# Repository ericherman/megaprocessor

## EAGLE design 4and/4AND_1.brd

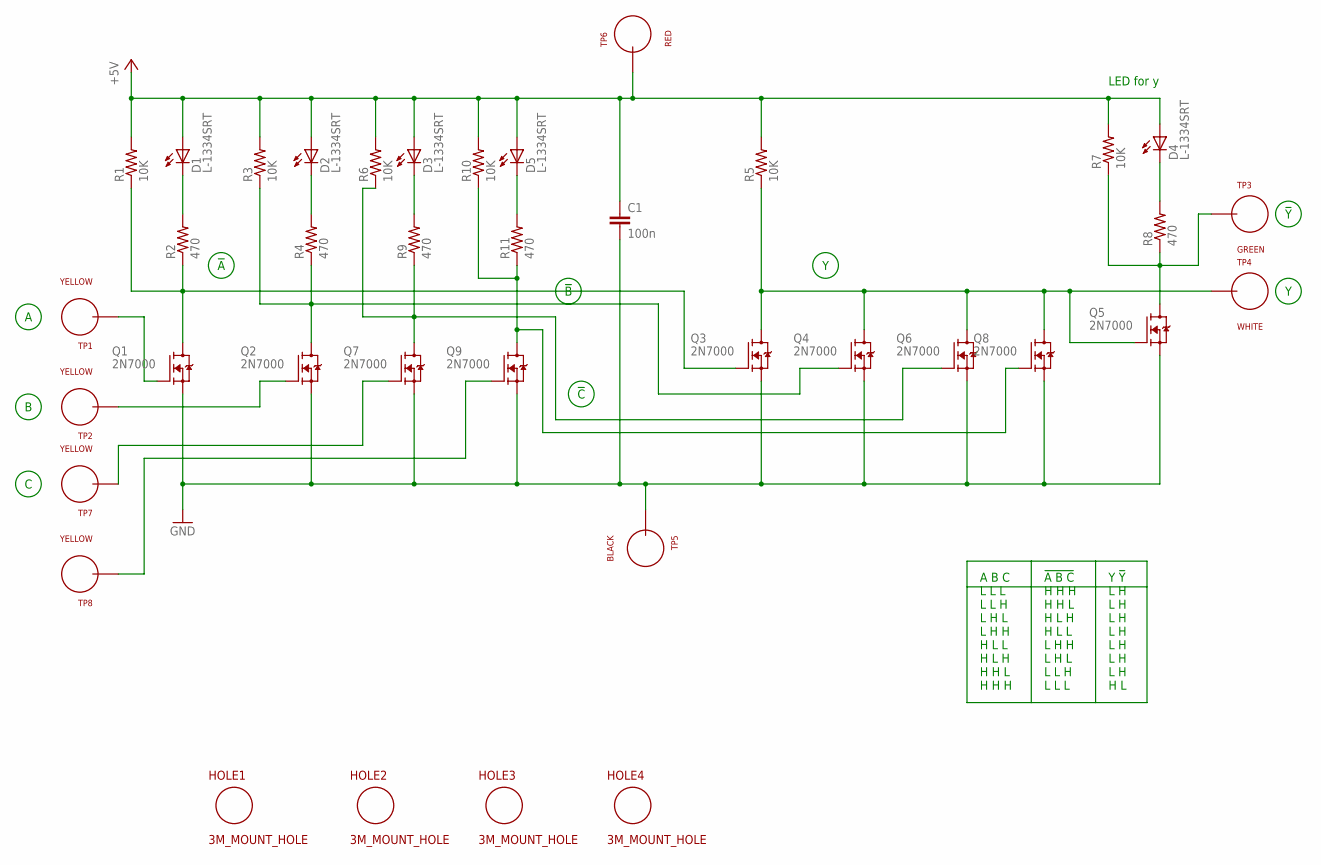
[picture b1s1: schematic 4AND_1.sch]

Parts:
C1: 100n; CAP_P2INCH
D1, D2, D3, D4, D5: L-1334SRT; LED3MM
HOLE1, HOLE2, HOLE3, HOLE4: 3M_MOUNT_HOLE; 3M_HOLE
Q1, Q2, Q3, Q4, Q5, Q6, Q7, Q8, Q9: 2N7000; TO92-DGS
R1, R3, R5, R6, R7, R10: 10K; R_P2INCH
R2, R4, R8, R9, R11: 470; R_P2INCH
TP1, TP2, TP7, TP8: YELLOW; TEST_LOOP
TP3: GREEN; TEST_LOOP
TP4: WHITE; TEST_LOOP
TP5: BLACK; TEST_LOOP
TP6: RED; TEST_LOOP

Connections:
+5V: C1.1, D1.A, D2.A, D3.A, D4.A, D5.A, R1.2, R3.2, R5.2, R6.2, R7.2, R10.2, TP6.P$1
GND: C1.2, Q1.S, Q2.S, Q3.S, Q4.S, Q5.S, Q6.S, Q7.S, Q8.S, Q9.S, TP5.P$1
unnamed: Q3.D, Q4.D, Q5.G, Q6.D, Q8.D, R5.1, TP4.P$1
unnamed: D3.K (C), R9.2
unnamed: D4.K (C), R8.2
unnamed: Q5.D, R7.1, R8.1, TP3.P$1
unnamed: Q6.G, Q7.D, R6.1, R9.1
unnamed: D2.K (C), R4.2
unnamed: Q2.D, Q4.G, R3.1, R4.1
unnamed: D1.K (C), R2.2
unnamed: Q1.D, Q3.G, R1.1, R2.1
unnamed: Q7.G, TP7.P$1
unnamed: Q1.G, TP1.P$1
unnamed: Q2.G, TP2.P$1
unnamed: D5.K (C), R11.2
unnamed: Q9.G, TP8.P$1
unnamed: Q8.G, Q9.D, R10.1, R11.1

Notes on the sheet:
A B C L L L L L H L H L L H H H L L H L H H H L H H H
!A B C H H H H H L H L H H L L L H H L H L L L H L L L
Y !Y L H L H L H L H L H L H L H H L
LED for y

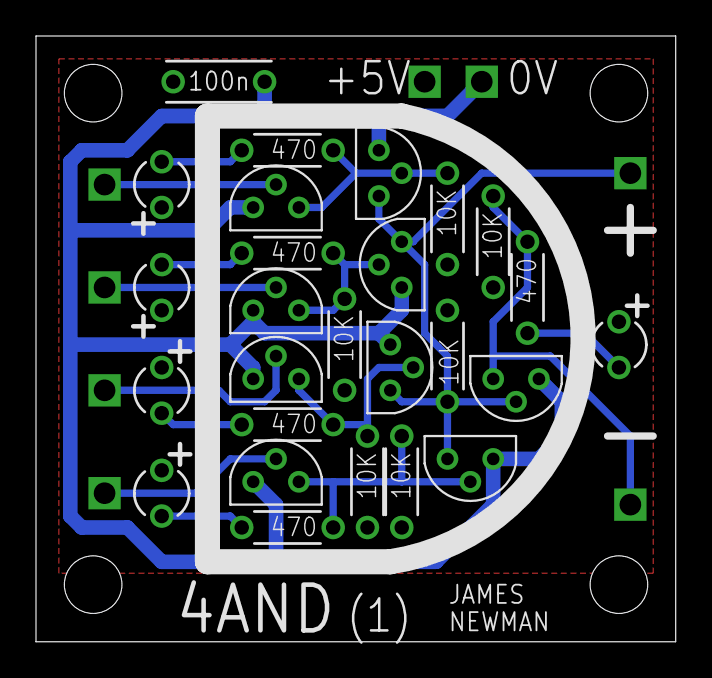
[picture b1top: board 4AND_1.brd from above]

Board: 2 copper layers, 35.5 x 33.7 mm, 38 parts (0 on the bottom side), 17 nets.

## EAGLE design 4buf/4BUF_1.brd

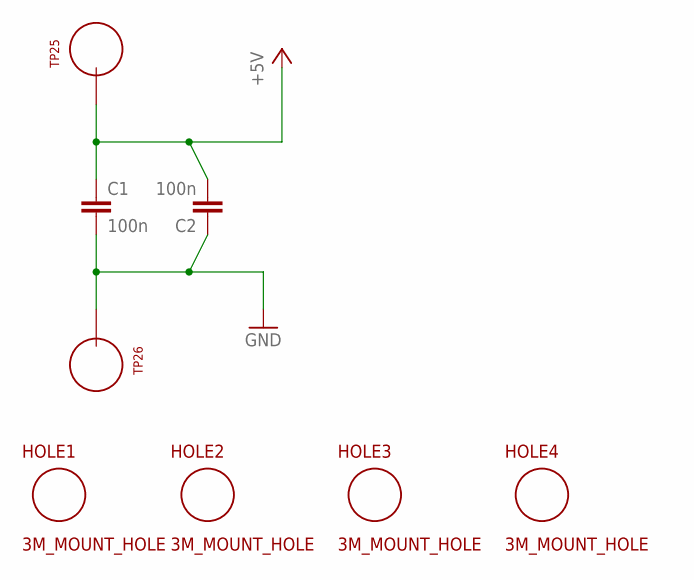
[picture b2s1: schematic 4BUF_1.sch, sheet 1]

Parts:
C1, C2: 100n; CAP_P2INCH
HOLE1, HOLE2, HOLE3, HOLE4: 3M_MOUNT_HOLE; 3M_HOLE
TP25, TP26: TEST_LOOP

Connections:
+5V: C1.1, C2.2, TP25.P$1; also elsewhere on the board
GND: C1.2, C2.1, TP26.P$1; also elsewhere on the board

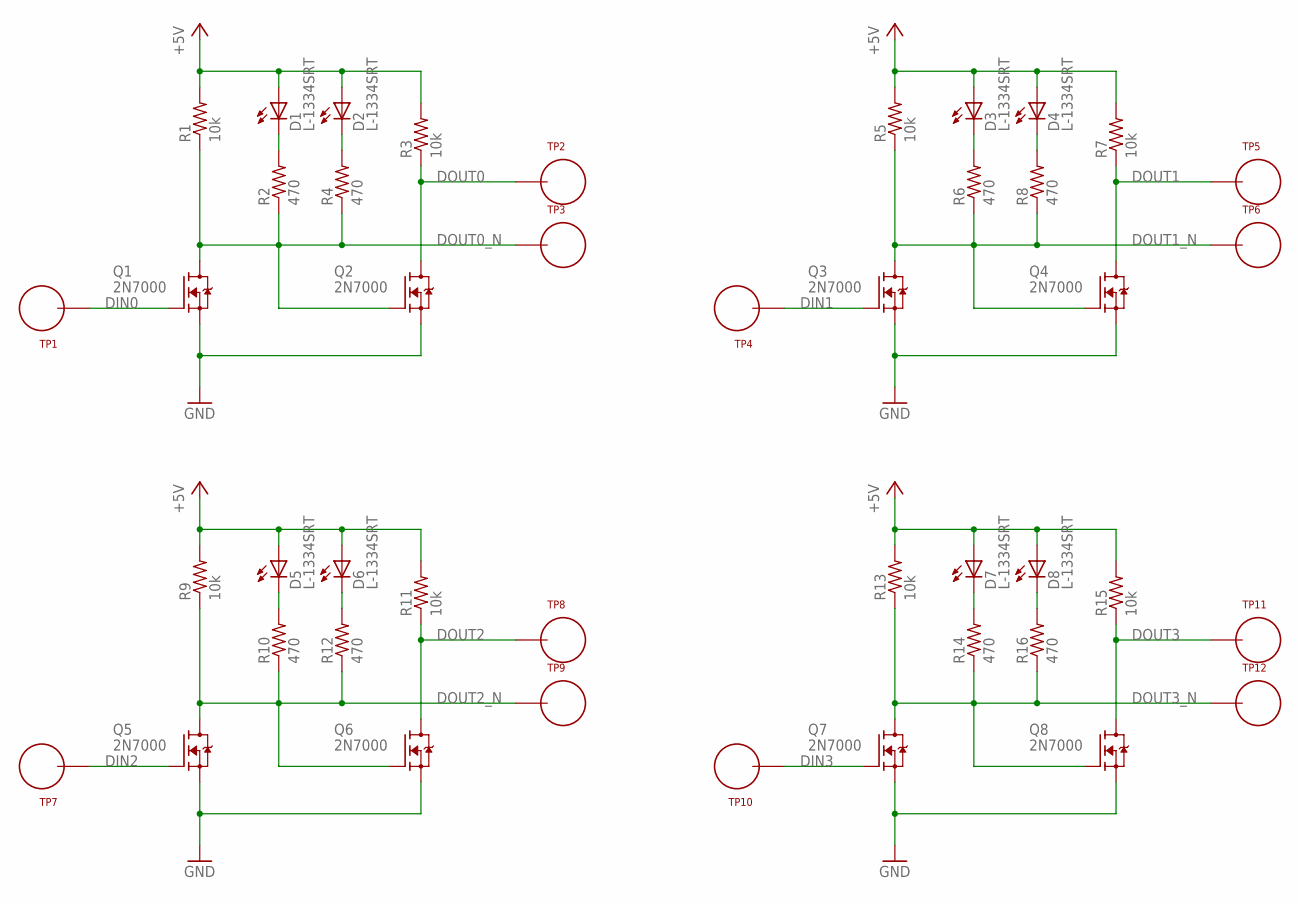
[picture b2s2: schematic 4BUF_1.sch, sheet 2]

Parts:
D1, D2, D3, D4, D5, D6, D7, D8: L-1334SRT; LED3MM
Q1, Q2, Q3, Q4, Q5, Q6, Q7, Q8: 2N7000; TO92-DGS
R1, R3, R5, R7, R9, R11, R13, R15: 10k; R_P2INCH
R2, R4, R6, R8, R10, R12, R14, R16: 470; R_P2INCH
TP1, TP2, TP3, TP4, TP5, TP6, TP7, TP8, TP9, TP10, TP11, TP12: TEST_LOOP

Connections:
+5V: D1.A, D2.A, D3.A, D4.A, D5.A, D6.A, D7.A, D8.A, R1.2, R3.2, R5.2, R7.2, R9.2, R11.2, R13.2, R15.2; also elsewhere on the board
DIN0: Q1.G, TP1.P$1
DIN1: Q3.G, TP4.P$1
DIN2: Q5.G, TP7.P$1
DIN3: Q7.G, TP10.P$1
DOUT0: Q2.D, R3.1, TP2.P$1
DOUT0_N: Q1.D, Q2.G, R1.1, R2.1, R4.1, TP3.P$1
DOUT1: Q4.D, R7.1, TP5.P$1
DOUT1_N: Q3.D, Q4.G, R5.1, R6.1, R8.1, TP6.P$1
DOUT2: Q6.D, R11.1, TP8.P$1
DOUT2_N: Q5.D, Q6.G, R9.1, R10.1, R12.1, TP9.P$1
DOUT3: Q8.D, R15.1, TP11.P$1
DOUT3_N: Q7.D, Q8.G, R13.1, R14.1, R16.1, TP12.P$1
GND: Q1.S, Q2.S, Q3.S, Q4.S, Q5.S, Q6.S, Q7.S, Q8.S; also elsewhere on the board
unnamed: D2.K (C), R4.2
unnamed: D1.K (C), R2.2
unnamed: D3.K (C), R6.2
unnamed: D4.K (C), R8.2
unnamed: D5.K (C), R10.2
unnamed: D6.K (C), R12.2
unnamed: D7.K (C), R14.2
unnamed: D8.K (C), R16.2

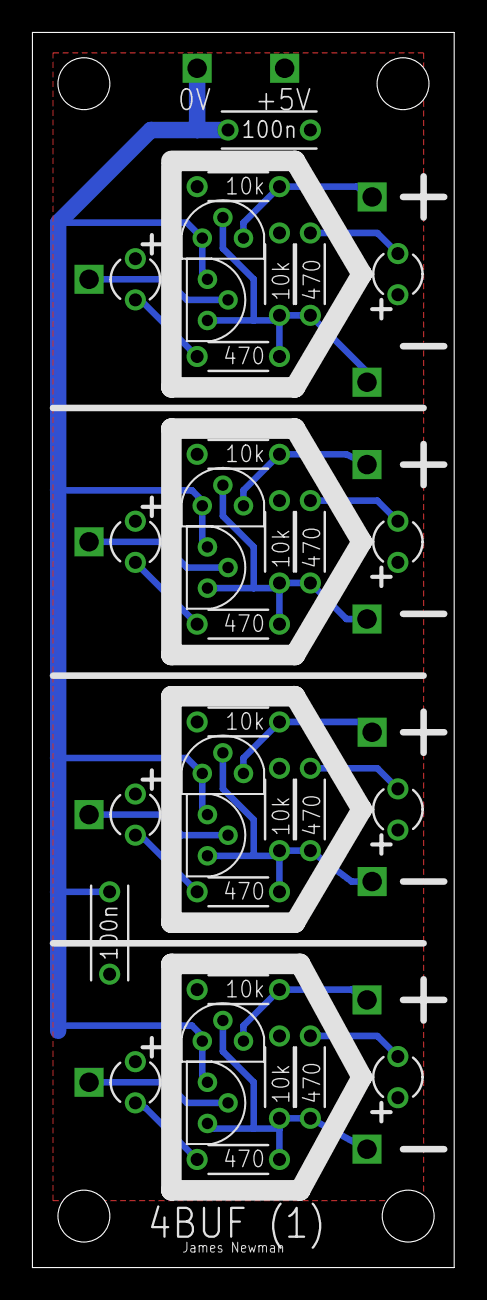
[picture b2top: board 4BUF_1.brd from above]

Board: 2 copper layers, 26.0 x 76.2 mm, 52 parts (0 on the bottom side), 22 nets.

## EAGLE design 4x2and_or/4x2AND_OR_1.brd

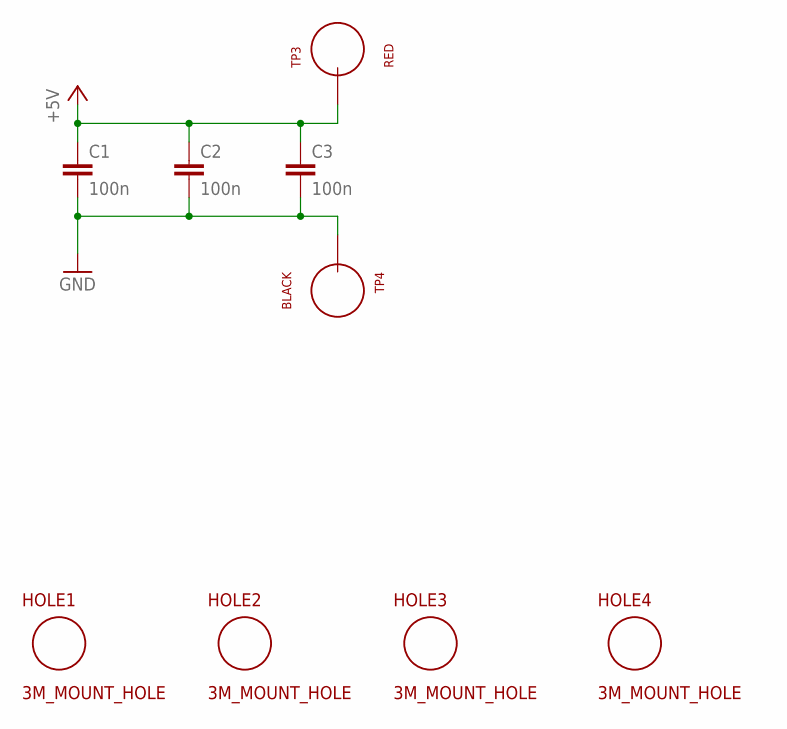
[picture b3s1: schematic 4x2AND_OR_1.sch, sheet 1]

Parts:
C1, C2, C3: 100n; CAP_P2INCH
HOLE1, HOLE2, HOLE3, HOLE4: 3M_MOUNT_HOLE; 3M_HOLE
TP3: RED; TEST_LOOP
TP4: BLACK; TEST_LOOP

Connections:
+5V: C1.1, C2.1, C3.1, TP3.P$1; also elsewhere on the board
GND: C1.2, C2.2, C3.2, TP4.P$1; also elsewhere on the board

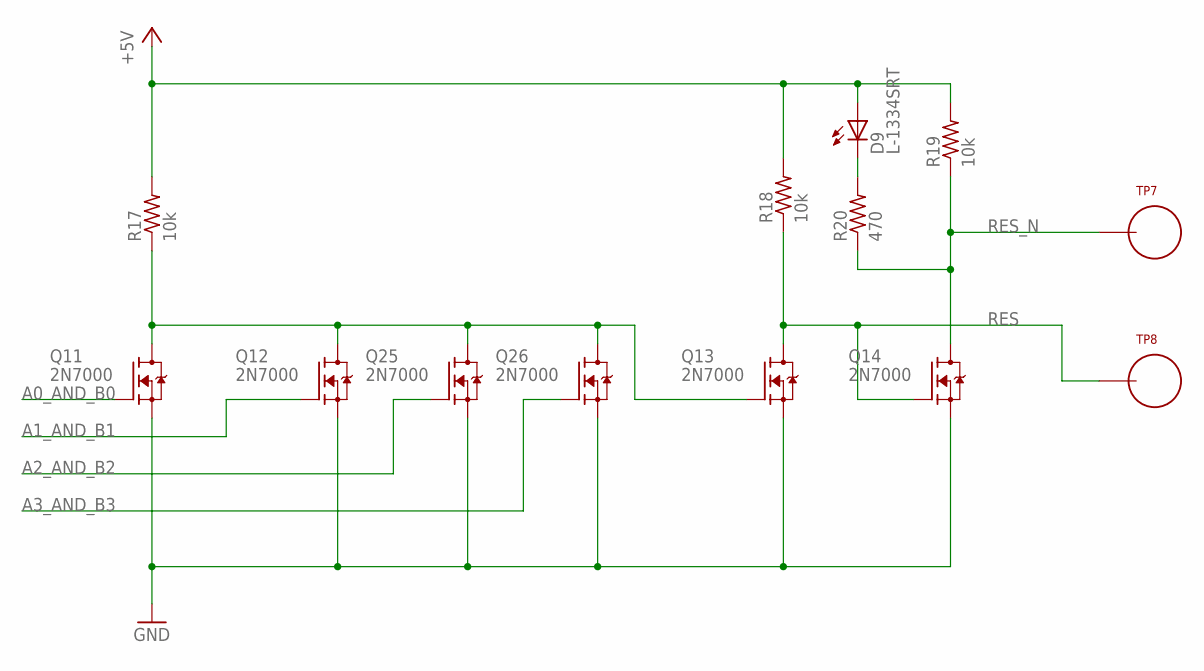
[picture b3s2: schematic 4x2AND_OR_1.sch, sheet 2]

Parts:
D9: L-1334SRT; LED3MM
Q11, Q12, Q13, Q14, Q25, Q26: 2N7000; TO92-DGS
R17, R18, R19: 10k; R_P2INCH
R20: 470; R_P2INCH
TP7, TP8: TEST_LOOP

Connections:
+5V: D9.A, R17.2, R18.2, R19.2; also elsewhere on the board
A0_AND_B0: Q11.G; also elsewhere on the board
A1_AND_B1: Q12.G; also elsewhere on the board
A2_AND_B2: Q25.G; also elsewhere on the board
A3_AND_B3: Q26.G; also elsewhere on the board
GND: Q11.S, Q12.S, Q13.S, Q14.S, Q25.S, Q26.S; also elsewhere on the board
unnamed: Q11.D, Q12.D, Q13.G, Q25.D, Q26.D, R17.1
unnamed: D9.K (C), R20.2
RES: Q13.D, Q14.G, R18.1, TP8.P$1
RES_N: Q14.D, R19.1, R20.1, TP7.P$1

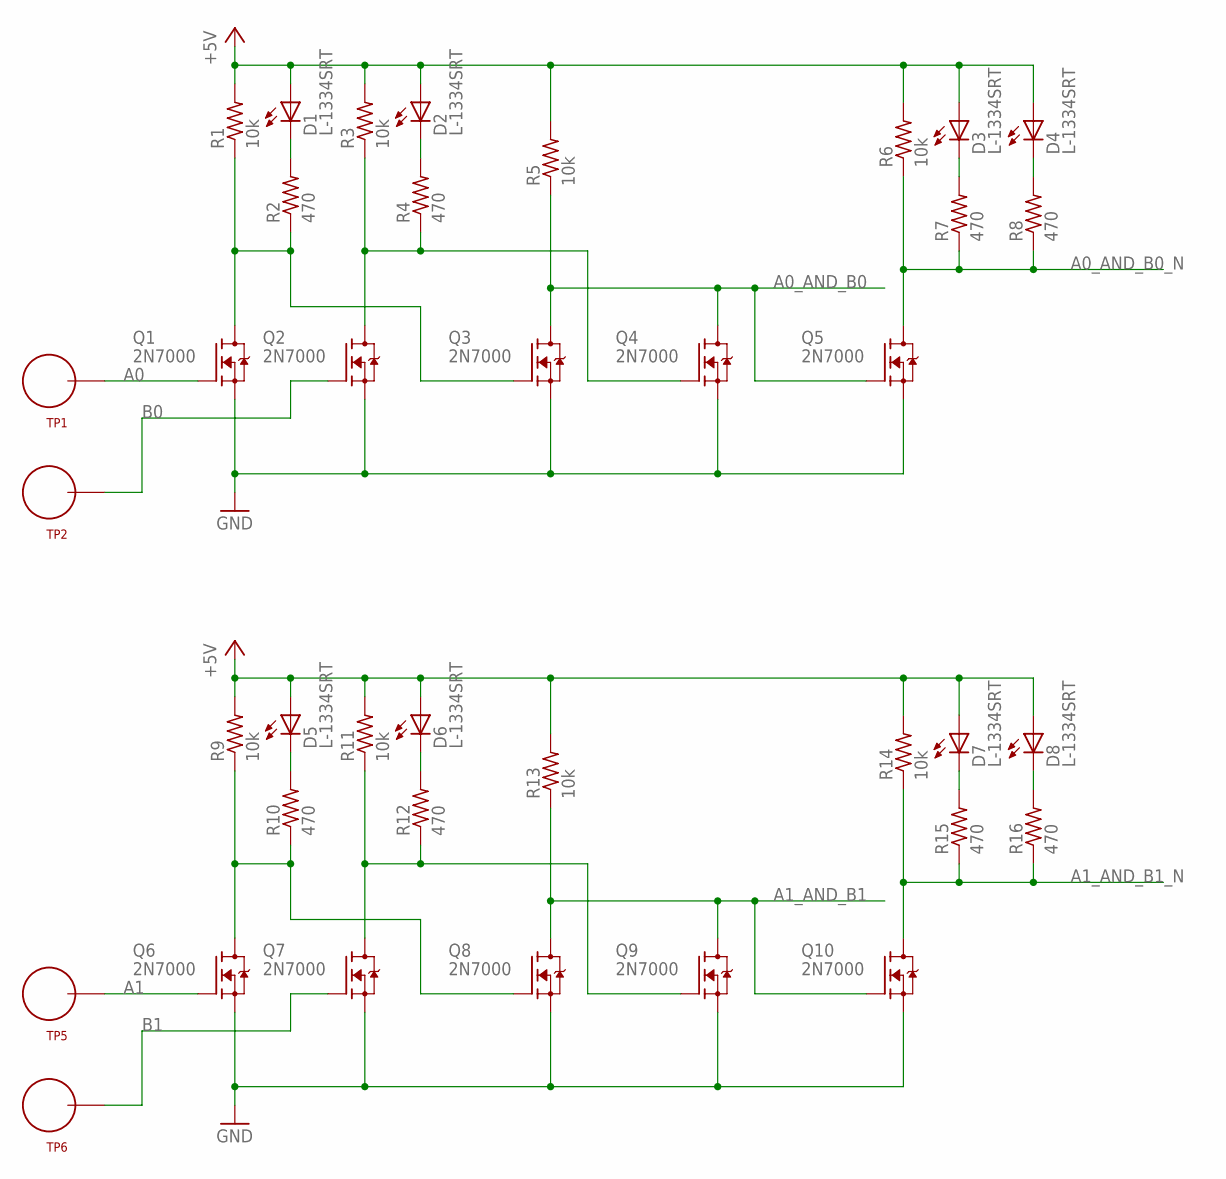
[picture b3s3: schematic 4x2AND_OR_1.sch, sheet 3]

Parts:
D1, D2, D3, D4, D5, D6, D7, D8: L-1334SRT; LED3MM
Q1, Q2, Q3, Q4, Q5, Q6, Q7, Q8, Q9, Q10: 2N7000; TO92-DGS
R1, R3, R5, R6, R9, R11, R13, R14: 10k; R_P2INCH
R2, R4, R7, R8, R10, R12, R15, R16: 470; R_P2INCH
TP1, TP2, TP5, TP6: TEST_LOOP

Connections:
+5V: D1.A, D2.A, D3.A, D4.A, D5.A, D6.A, D7.A, D8.A, R1.2, R3.2, R5.2, R6.2, R9.2, R11.2, R13.2, R14.2; also elsewhere on the board
A0: Q1.G, TP1.P$1
A0_AND_B0: Q3.D, Q4.D, Q5.G, R5.1; also elsewhere on the board
A0_AND_B0_N: Q5.D, R6.1, R7.1, R8.1
A1: Q6.G, TP5.P$1
A1_AND_B1: Q8.D, Q9.D, Q10.G, R13.1; also elsewhere on the board
A1_AND_B1_N: Q10.D, R14.1, R15.1, R16.1
B0: Q2.G, TP2.P$1
B1: Q7.G, TP6.P$1
GND: Q1.S, Q2.S, Q3.S, Q4.S, Q5.S, Q6.S, Q7.S, Q8.S, Q9.S, Q10.S; also elsewhere on the board
unnamed: D1.K (C), R2.2
unnamed: Q1.D, Q3.G, R1.1, R2.1
unnamed: D4.K (C), R8.2
unnamed: D2.K (C), R4.2
unnamed: Q2.D, Q4.G, R3.1, R4.1
unnamed: D5.K (C), R10.2
unnamed: Q6.D, Q8.G, R9.1, R10.1
unnamed: D6.K (C), R12.2
unnamed: D3.K (C), R7.2
unnamed: Q7.D, Q9.G, R11.1, R12.1
unnamed: D7.K (C), R15.2
unnamed: D8.K (C), R16.2

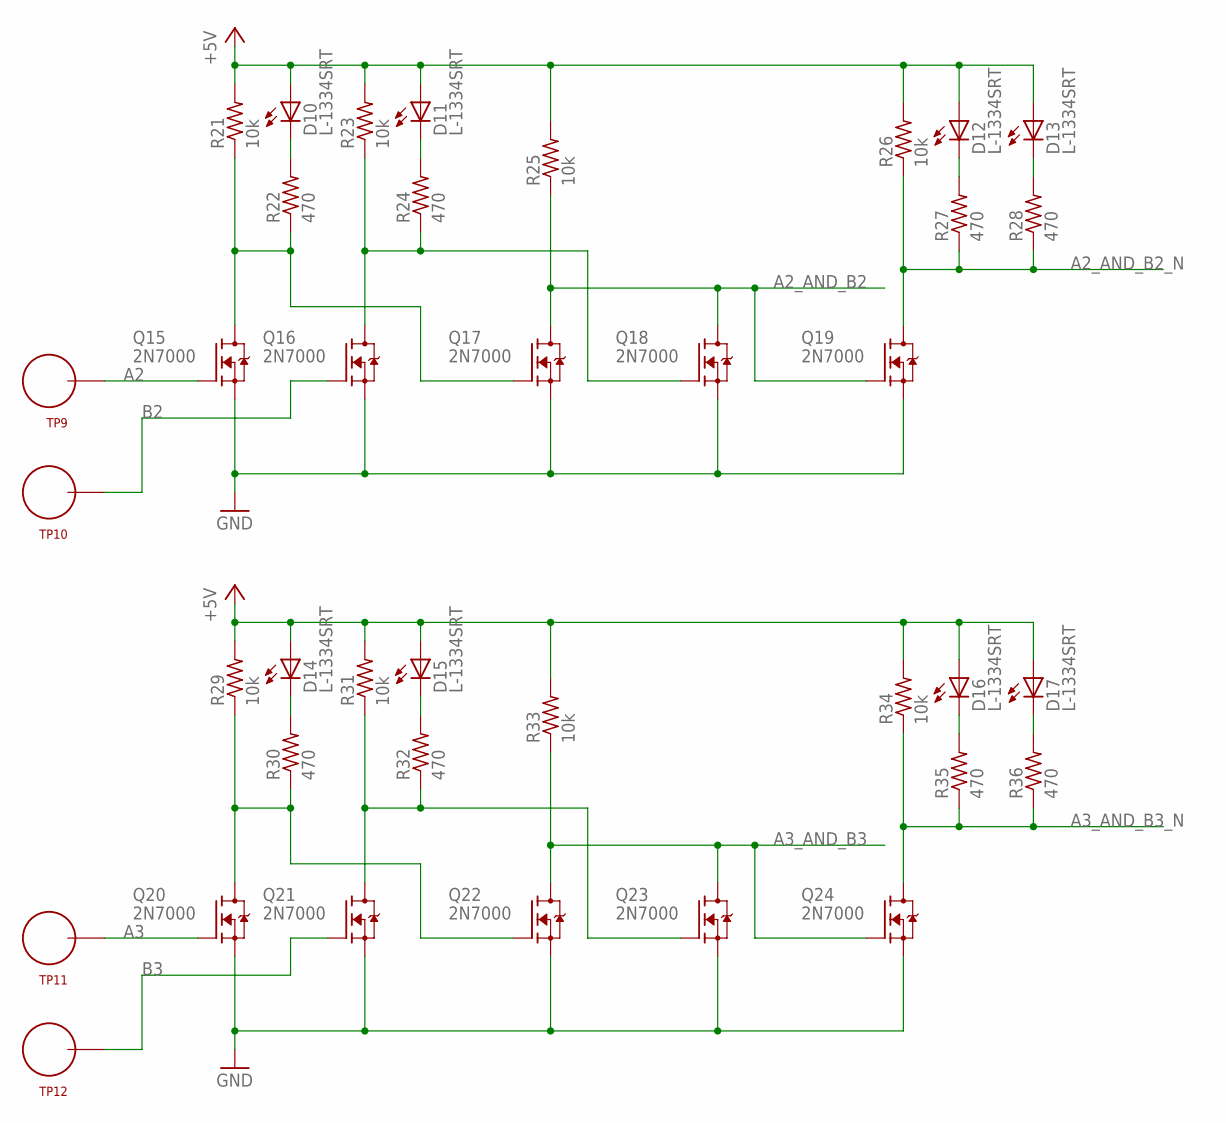
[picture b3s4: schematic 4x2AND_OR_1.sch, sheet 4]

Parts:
D10, D11, D12, D13, D14, D15, D16, D17: L-1334SRT; LED3MM
Q15, Q16, Q17, Q18, Q19, Q20, Q21, Q22, Q23, Q24: 2N7000; TO92-DGS
R21, R23, R25, R26, R29, R31, R33, R34: 10k; R_P2INCH
R22, R24, R27, R28, R30, R32, R35, R36: 470; R_P2INCH
TP9, TP10, TP11, TP12: TEST_LOOP

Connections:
+5V: D10.A, D11.A, D12.A, D13.A, D14.A, D15.A, D16.A, D17.A, R21.2, R23.2, R25.2, R26.2, R29.2, R31.2, R33.2, R34.2; also elsewhere on the board
A2: Q15.G, TP9.P$1
A2_AND_B2: Q17.D, Q18.D, Q19.G, R25.1; also elsewhere on the board
A2_AND_B2_N: Q19.D, R26.1, R27.1, R28.1
A3: Q20.G, TP11.P$1
A3_AND_B3: Q22.D, Q23.D, Q24.G, R33.1; also elsewhere on the board
A3_AND_B3_N: Q24.D, R34.1, R35.1, R36.1
B2: Q16.G, TP10.P$1
B3: Q21.G, TP12.P$1
GND: Q15.S, Q16.S, Q17.S, Q18.S, Q19.S, Q20.S, Q21.S, Q22.S, Q23.S, Q24.S; also elsewhere on the board
unnamed: D10.K (C), R22.2
unnamed: Q15.D, Q17.G, R21.1, R22.1
unnamed: D11.K (C), R24.2
unnamed: Q16.D, Q18.G, R23.1, R24.1
unnamed: D12.K (C), R27.2
unnamed: D13.K (C), R28.2
unnamed: D14.K (C), R30.2
unnamed: Q20.D, Q22.G, R29.1, R30.1
unnamed: D15.K (C), R32.2
unnamed: Q21.D, Q23.G, R31.1, R32.1
unnamed: D16.K (C), R35.2
unnamed: D17.K (C), R36.2

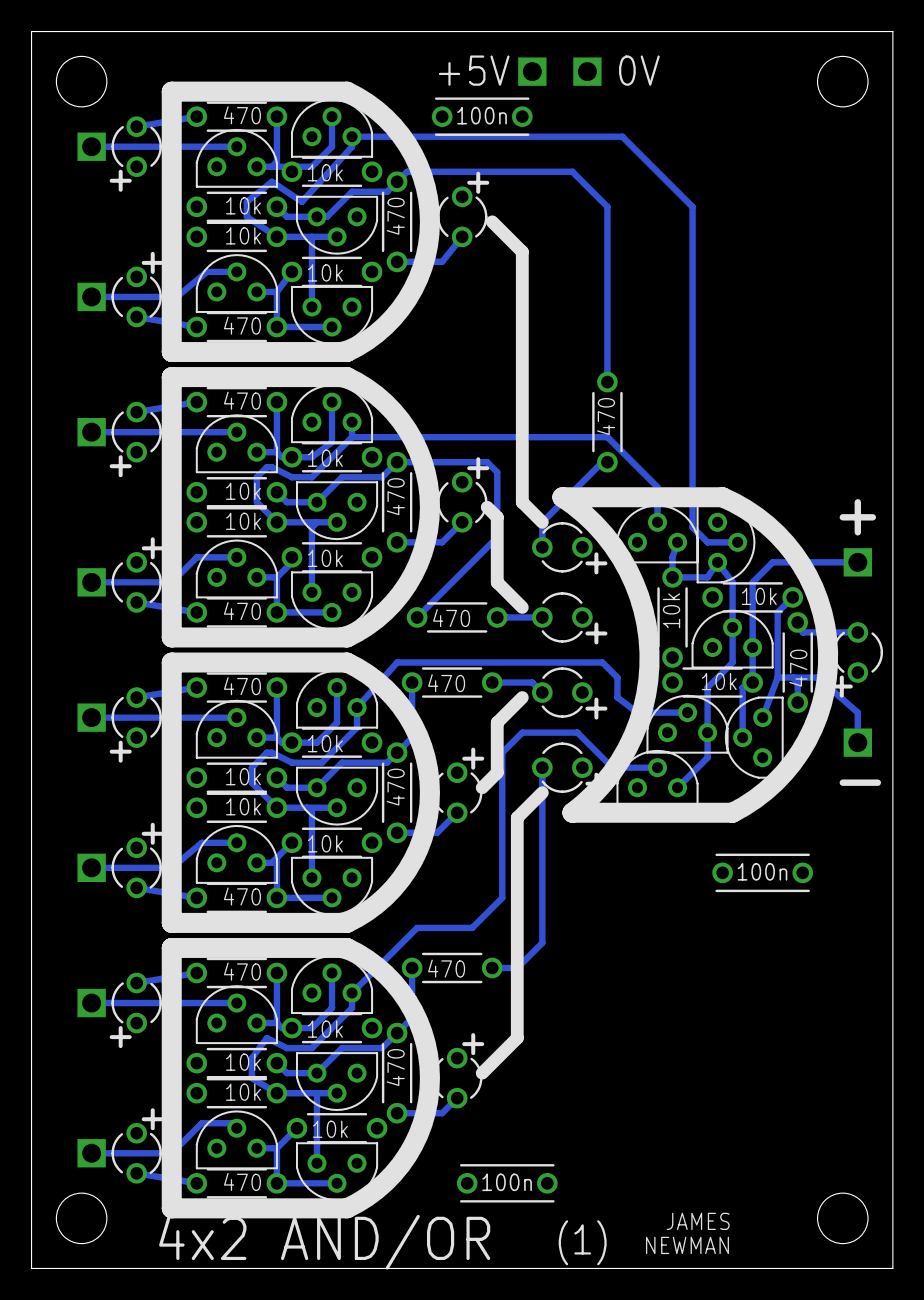
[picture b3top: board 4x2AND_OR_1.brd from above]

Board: 4 copper layers, 54.6 x 78.4 mm, 98 parts (0 on the bottom side), 46 nets.

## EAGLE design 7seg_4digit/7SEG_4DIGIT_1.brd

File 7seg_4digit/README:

3x2, 4DIGITS

Same board, there's two ways of fitting the display.

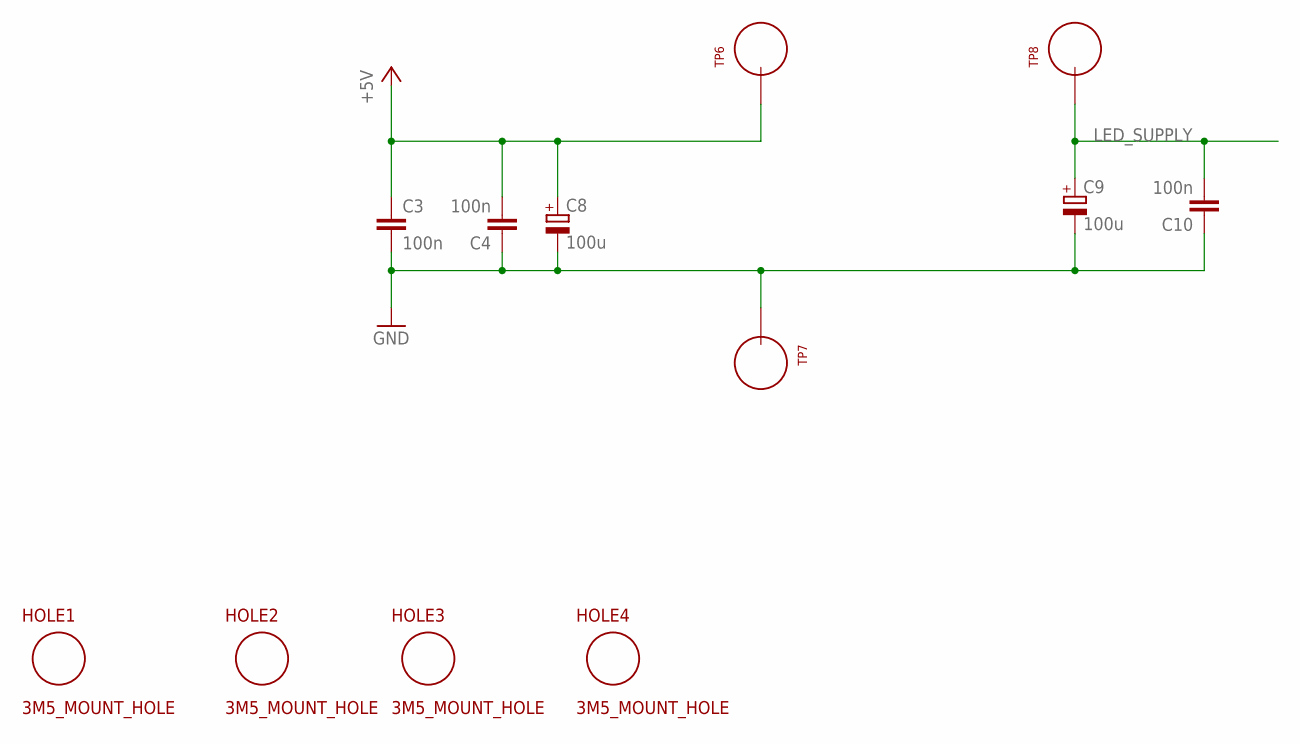
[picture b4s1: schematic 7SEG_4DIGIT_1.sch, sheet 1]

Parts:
C3, C4, C10: 100n; CAP_P2INCH
C8, C9: 100u; POLARISED_CAP_2P5_6P3MM
HOLE1, HOLE2, HOLE3, HOLE4: 3M5_MOUNT_HOLE; 3P5M_HOLE
TP6, TP7, TP8: TEST_LOOP

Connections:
+5V: C3.1, C4.2, C8.A, TP6.P$1; also elsewhere on the board
GND: C3.2, C4.1, C8.K, C9.K, C10.1, TP7.P$1; also elsewhere on the board
LED_SUPPLY: C9.A, C10.2, TP8.P$1; also elsewhere on the board

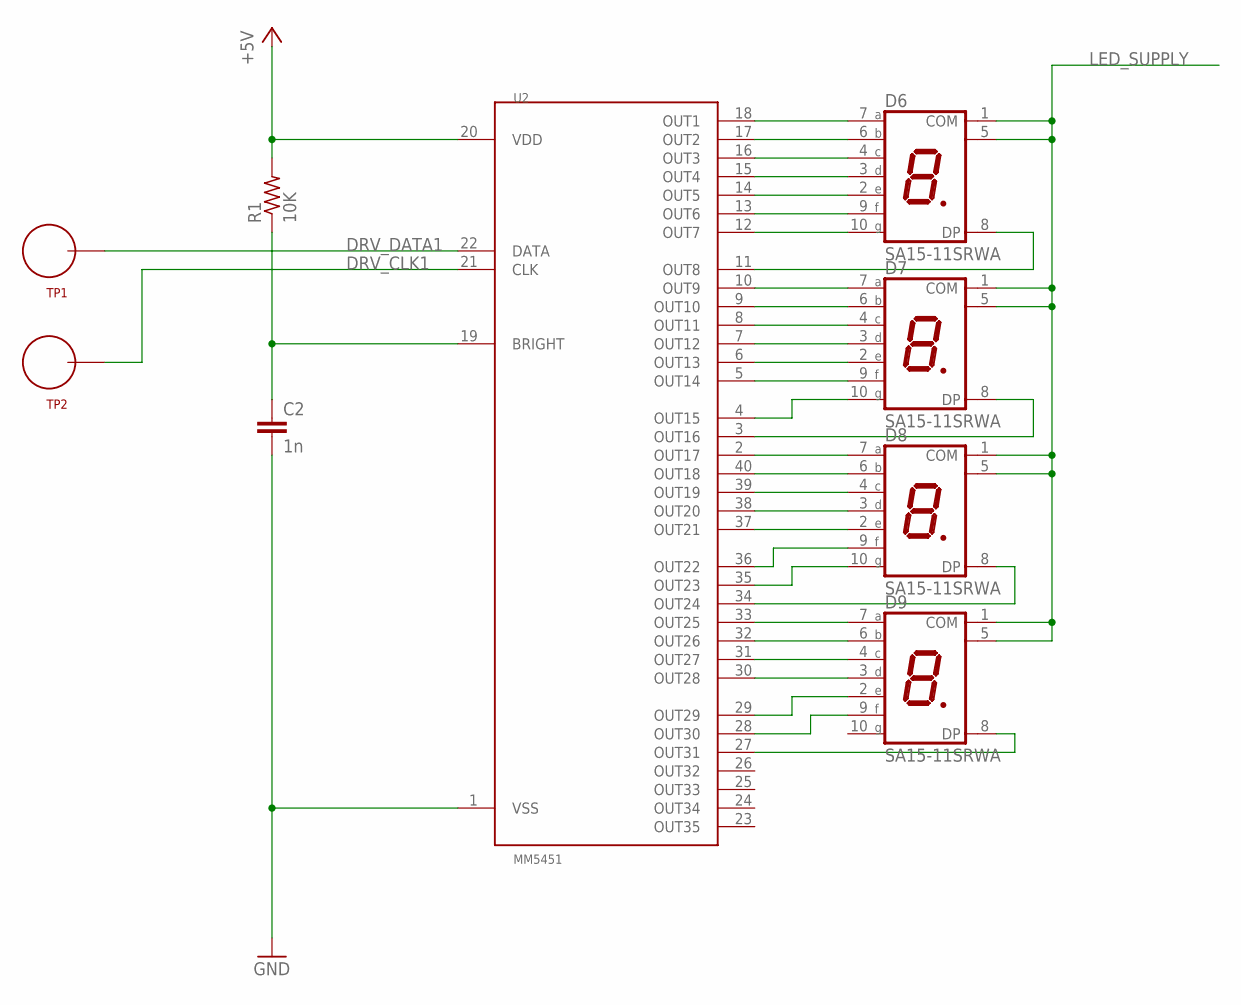
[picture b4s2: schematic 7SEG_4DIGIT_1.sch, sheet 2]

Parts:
C2: 1n; CAP_P2INCH
D6, D7, D8, D9: SA15-11SRWA; SC15
R1: 10K; R_P2INCH
TP1, TP2: TEST_LOOP
U2: MM5451; DIP40_P6

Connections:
+5V: R1.2, U2.20 (VDD); also elsewhere on the board
DRV_CLK1: TP2.P$1, U2.21 (CLK)
DRV_DATA1: TP1.P$1, U2.22 (DATA)
GND: C2.2, U2.1 (VSS); also elsewhere on the board
LED_SUPPLY: D6.1 (COM), D6.5 (COM), D7.1 (COM), D7.5 (COM), D8.1 (COM), D8.5 (COM), D9.1 (COM), D9.5 (COM); also elsewhere on the board
unnamed: D6.8 (DP), U2.11 (OUT8)
unnamed: D7.7 (A), U2.10 (OUT9)
unnamed: D7.6 (B), U2.9 (OUT10)
unnamed: C2.1, R1.1, U2.19 (BRIGHT)
unnamed: D7.4 (C), U2.8 (OUT11)
unnamed: D7.3 (D), U2.7 (OUT12)
unnamed: D7.2 (E), U2.6 (OUT13)
unnamed: D7.9 (F), U2.5 (OUT14)
unnamed: D7.10 (G), U2.4 (OUT15)
unnamed: D6.7 (A), U2.18 (OUT1)
unnamed: D6.6 (B), U2.17 (OUT2)
unnamed: D6.4 (C), U2.16 (OUT3)
unnamed: D6.3 (D), U2.15 (OUT4)
unnamed: D6.2 (E), U2.14 (OUT5)
unnamed: D6.9 (F), U2.13 (OUT6)
unnamed: D6.10 (G), U2.12 (OUT7)
unnamed: D7.8 (DP), U2.3 (OUT16)
unnamed: D8.7 (A), U2.2 (OUT17)
unnamed: D8.6 (B), U2.40 (OUT18)
unnamed: D8.4 (C), U2.39 (OUT19)
unnamed: D8.3 (D), U2.38 (OUT20)
unnamed: D8.2 (E), U2.37 (OUT21)
unnamed: D8.9 (F), U2.36 (OUT22)
unnamed: D8.10 (G), U2.35 (OUT23)
unnamed: D8.8 (DP), U2.34 (OUT24)
unnamed: D9.7 (A), U2.33 (OUT25)
unnamed: D9.6 (B), U2.32 (OUT26)
unnamed: D9.4 (C), U2.31 (OUT27)
unnamed: D9.3 (D), U2.30 (OUT28)
unnamed: D9.2 (E), U2.29 (OUT29)
unnamed: D9.9 (F), U2.28 (OUT30)
unnamed: D9.8 (DP), U2.27 (OUT31)

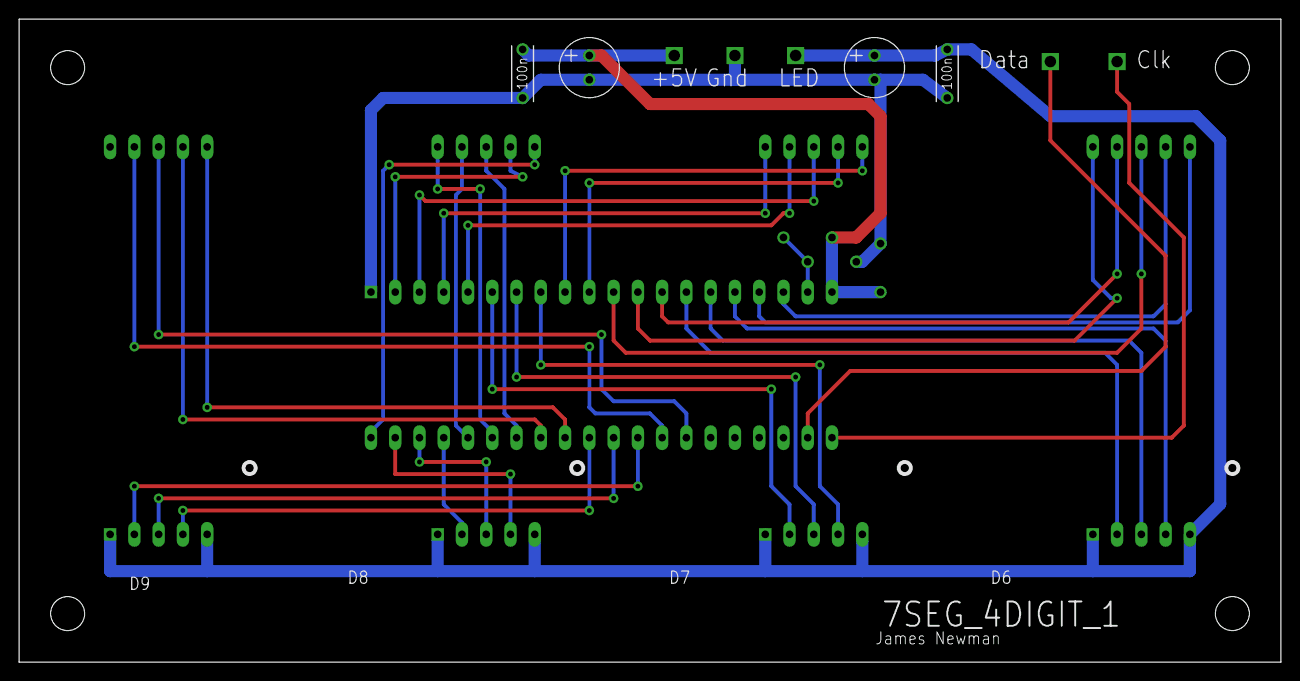
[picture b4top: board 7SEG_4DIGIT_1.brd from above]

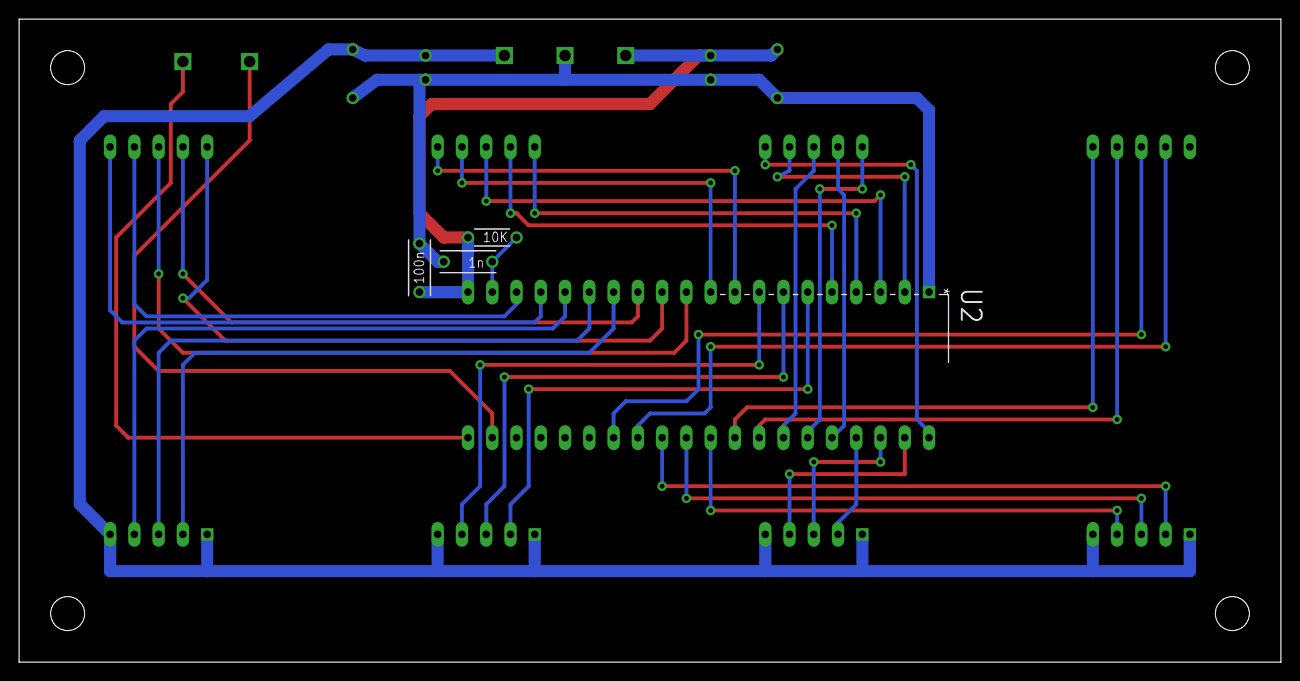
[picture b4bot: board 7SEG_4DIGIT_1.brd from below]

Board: 2 copper layers, 132.1 x 67.3 mm, 21 parts (4 on the bottom side), 37 nets.

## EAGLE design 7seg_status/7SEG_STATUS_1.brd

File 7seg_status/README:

STATUS_DISPLAY

Used for state machine and status flags, only does 0 & 1, or - & 1.

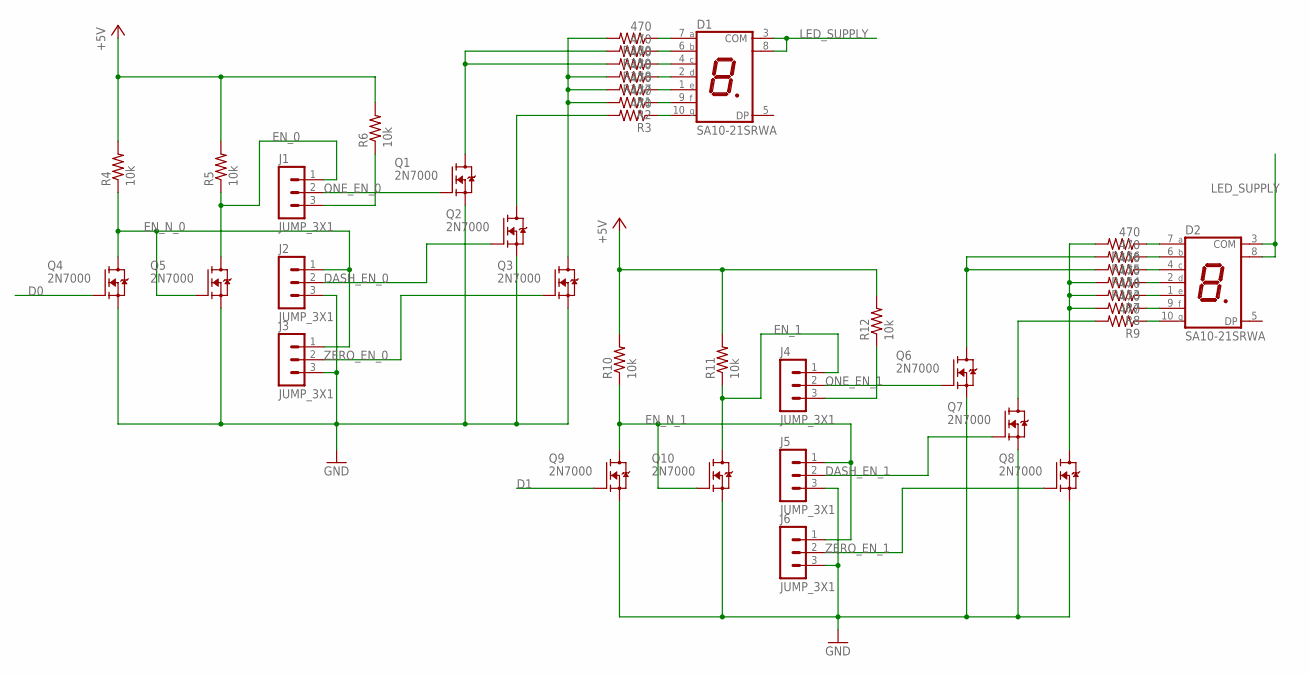
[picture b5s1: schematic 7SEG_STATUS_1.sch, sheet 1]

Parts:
D1, D2: SA10-21SRWA; SA10
J1, J2, J3, J4, J5, J6: JUMP_3X1
Q1, Q2, Q3, Q4, Q5, Q6, Q7, Q8, Q9, Q10: 2N7000; TO92-DGS
R1, R2, R3, R7, R8, R9, R153, R154, R155, R156, R157, R158, R159, R160: 470; R_P2INCH
R4, R5, R6, R10, R11, R12: 10k; R_P2INCH

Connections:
+5V: R4.2, R5.2, R6.2, R10.2, R11.2, R12.2; also elsewhere on the board
D0: Q4.G; also elsewhere on the board
D1: Q9.G; also elsewhere on the board
DASH_EN_0: J2.2, Q2.G
DASH_EN_1: J5.2, Q7.G
EN_0: J1.1, Q5.D, R5.1
EN_1: J4.1, Q10.D, R11.1
EN_N_0: J2.1, J3.1, Q4.D, Q5.G, R4.1
EN_N_1: J5.1, J6.1, Q9.D, Q10.G, R10.1
GND: J2.3, J3.3, J5.3, J6.3, Q1.S, Q2.S, Q3.S, Q4.S, Q5.S, Q6.S, Q7.S, Q8.S, Q9.S, Q10.S; also elsewhere on the board
LED_SUPPLY: D1.3 (COM), D1.8 (COM), D2.3 (COM), D2.8 (COM); also elsewhere on the board
unnamed: D2.7 (A), R156.1
unnamed: D2.6 (B), R155.1
unnamed: D2.4 (C), R154.1
unnamed: D2.2 (D), R153.1
unnamed: D1.7 (A), R160.1
unnamed: D2.1 (E), R7.1
unnamed: D2.9 (F), R8.1
unnamed: J4.3, R12.1
unnamed: J1.3, R6.1
unnamed: D2.10 (G), R9.1
unnamed: Q7.D, R9.2
unnamed: Q6.D, R154.2, R155.2
unnamed: Q8.D, R7.2, R8.2, R153.2, R156.2
unnamed: D1.6 (B), R159.1
unnamed: D1.4 (C), R158.1
unnamed: D1.2 (D), R157.1
unnamed: D1.1 (E), R1.1
unnamed: D1.9 (F), R2.1
unnamed: D1.10 (G), R3.1
unnamed: Q2.D, R3.2
unnamed: Q1.D, R158.2, R159.2
unnamed: Q3.D, R1.2, R2.2, R157.2, R160.2
ONE_EN_0: J1.2, Q1.G
ONE_EN_1: J4.2, Q6.G
ZERO_EN_0: J3.2, Q3.G
ZERO_EN_1: J6.2, Q8.G

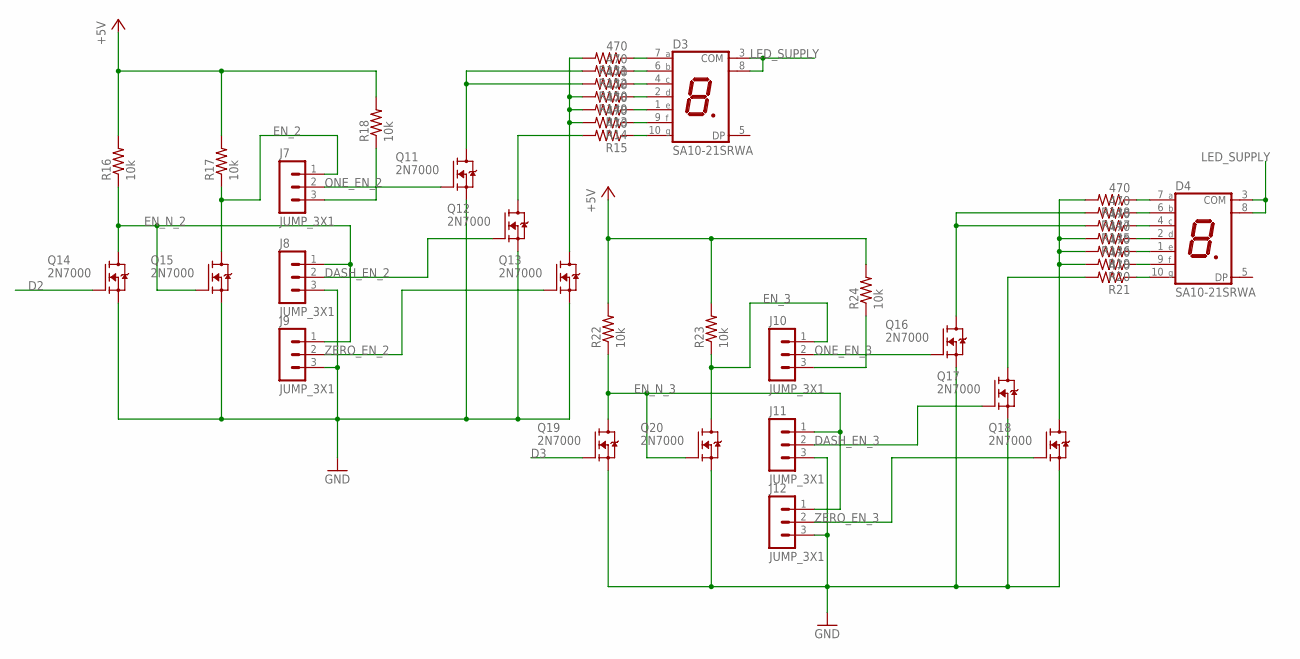
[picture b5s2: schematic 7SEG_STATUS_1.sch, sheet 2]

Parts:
D3, D4: SA10-21SRWA; SA10
J7, J8, J9, J10, J11, J12: JUMP_3X1
Q11, Q12, Q13, Q14, Q15, Q16, Q17, Q18, Q19, Q20: 2N7000; TO92-DGS
R13, R14, R15, R19, R20, R21, R145, R146, R147, R148, R149, R150, R151, R152: 470; R_P2INCH
R16, R17, R18, R22, R23, R24: 10k; R_P2INCH

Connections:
+5V: R16.2, R17.2, R18.2, R22.2, R23.2, R24.2; also elsewhere on the board
D2: Q14.G; also elsewhere on the board
D3: Q19.G; also elsewhere on the board
DASH_EN_2: J8.2, Q12.G
DASH_EN_3: J11.2, Q17.G
EN_2: J7.1, Q15.D, R17.1
EN_3: J10.1, Q20.D, R23.1
EN_N_2: J8.1, J9.1, Q14.D, Q15.G, R16.1
EN_N_3: J11.1, J12.1, Q19.D, Q20.G, R22.1
GND: J8.3, J9.3, J11.3, J12.3, Q11.S, Q12.S, Q13.S, Q14.S, Q15.S, Q16.S, Q17.S, Q18.S, Q19.S, Q20.S; also elsewhere on the board
LED_SUPPLY: D3.3 (COM), D3.8 (COM), D4.3 (COM), D4.8 (COM); also elsewhere on the board
unnamed: D3.7 (A), R151.1
unnamed: D4.7 (A), R148.1
unnamed: D4.6 (B), R147.1
unnamed: J7.3, R18.1
unnamed: D4.4 (C), R145.1
unnamed: D4.2 (D), R146.1
unnamed: D4.1 (E), R19.1
unnamed: D4.9 (F), R20.1
unnamed: J10.3, R24.1
unnamed: D4.10 (G), R21.1
unnamed: Q17.D, R21.2
unnamed: Q16.D, R145.2, R147.2
unnamed: Q18.D, R19.2, R20.2, R146.2, R148.2
unnamed: D3.6 (B), R152.1
unnamed: D3.4 (C), R150.1
unnamed: D3.2 (D), R149.1
unnamed: D3.1 (E), R13.1
unnamed: D3.9 (F), R14.1
unnamed: D3.10 (G), R15.1
unnamed: Q12.D, R15.2
unnamed: Q11.D, R150.2, R152.2
unnamed: Q13.D, R13.2, R14.2, R149.2, R151.2
ONE_EN_2: J7.2, Q11.G
ONE_EN_3: J10.2, Q16.G
ZERO_EN_2: J9.2, Q13.G
ZERO_EN_3: J12.2, Q18.G
